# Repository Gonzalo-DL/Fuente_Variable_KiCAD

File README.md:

Fuente de potencia variable con 2x LM317.

Ambos tienen la corriente limitada a aprox 1.5A.

Además uno de los dos lados tiene un limitador de corriente regulable hecho con otro LM317.

Ambos lados tienen las tierras separadas y hay salidas para conectar displays de voltage y corriente, switches y conectores.

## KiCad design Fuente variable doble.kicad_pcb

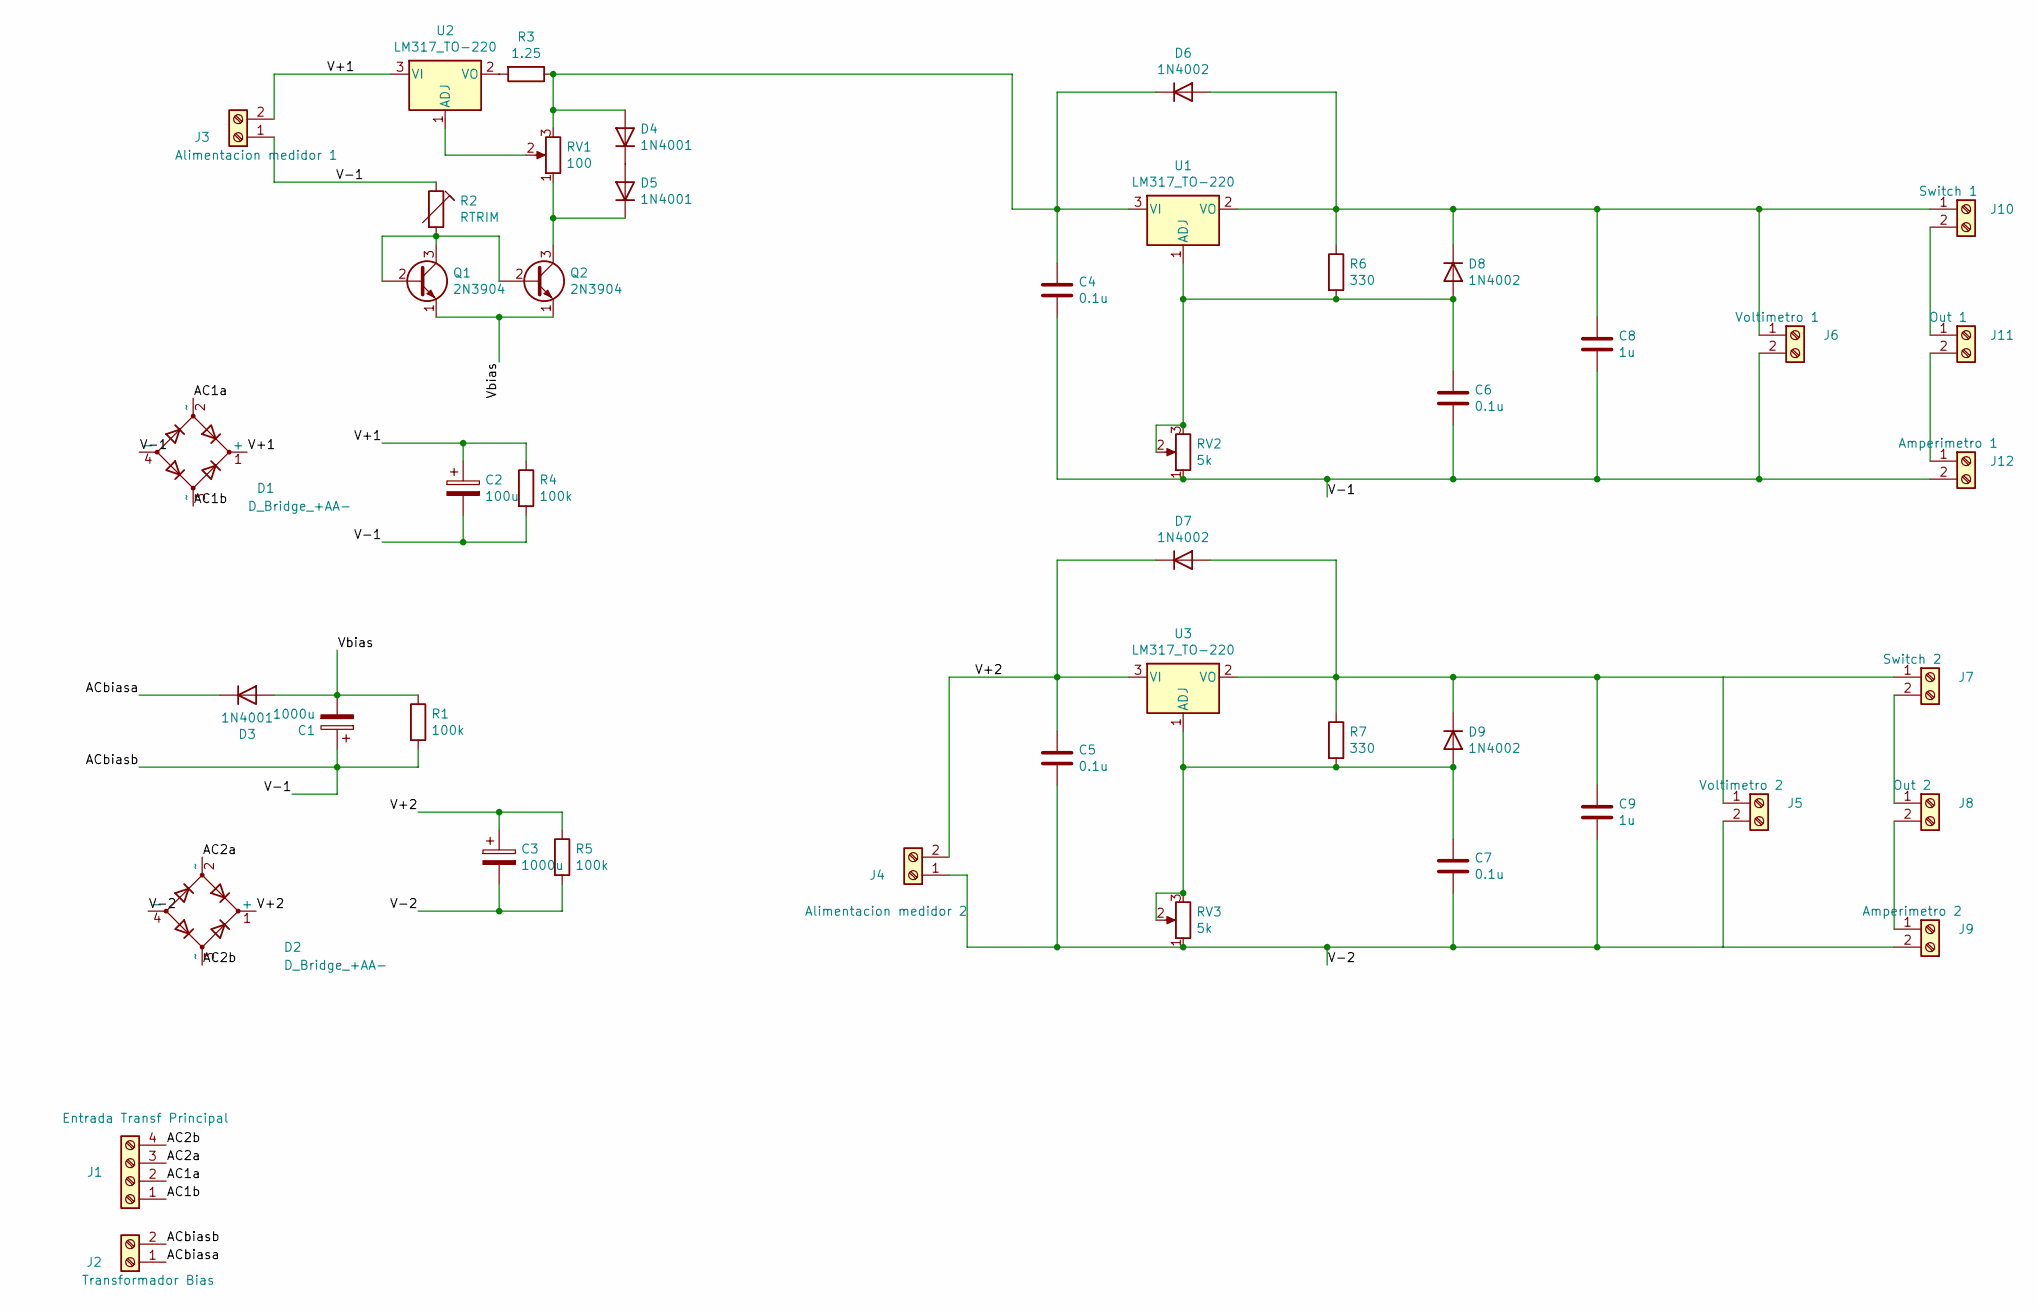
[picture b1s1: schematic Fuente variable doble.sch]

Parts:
C1, C3: 1000u; CP_Radial_D22.0mm_P10.00mm_SnapIn
C2: 100u; CP_Radial_D22.0mm_P10.00mm_SnapIn
C4, C5, C6, C7: 0.1u; C_Disc_D5.1mm_W3.2mm_P5.00mm
C8, C9: 1u; C_Disc_D5.1mm_W3.2mm_P5.00mm
D1, D2: D_Bridge_+AA-; TerminalBlock_MetzConnect_Type086_RT03404HBLC_1x04_P3.81mm_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
D3, D4, D5: 1N4001; D_DO-41_SOD81_P10.16mm_Horizontal
D6, D7, D8, D9: 1N4002; D_DO-41_SOD81_P10.16mm_Horizontal
J1: Entrada Transf Principal; TerminalBlock_bornier-4_P5.08mm
J2: Transformador Bias; TerminalBlock_bornier-2_P5.08mm
J3: Alimentacion medidor 1; TerminalBlock_bornier-2_P5.08mm
J4: Alimentacion medidor 2; TerminalBlock_bornier-2_P5.08mm
J5: Voltimetro 2; TerminalBlock_bornier-2_P5.08mm
J6: Voltimetro 1; TerminalBlock_bornier-2_P5.08mm
J7: Switch 2; TerminalBlock_bornier-2_P5.08mm
J8: Out 2; TerminalBlock_bornier-2_P5.08mm
J9: Amperimetro 2; TerminalBlock_bornier-2_P5.08mm
J10: Switch 1; TerminalBlock_bornier-2_P5.08mm
J11: Out 1; TerminalBlock_bornier-2_P5.08mm
J12: Amperimetro 1; TerminalBlock_bornier-2_P5.08mm
Q1, Q2: 2N3904; TO-92_Inline
R1, R4, R5: 100k; R_Axial_DIN0207_L6.3mm_D2.5mm_P10.16mm_Horizontal
R2: RTRIM; Potentiometer_Runtron_RM-063_Horizontal
R3: 1.25; R_Axial_DIN0207_L6.3mm_D2.5mm_P10.16mm_Horizontal
R6, R7: 330; R_Axial_DIN0207_L6.3mm_D2.5mm_P10.16mm_Horizontal
RV1: 100; Potentiometer_Alps_RK163_Single_Horizontal
RV2, RV3: 5k; Potentiometer_Alps_RK163_Single_Horizontal
U1, U2, U3: LM317_TO-220; TO-220-3_Vertical

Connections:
/AC1a: D1.2 (~~), J1.2
/AC1b: D1.3 (~~), J1.1
/AC2a: D2.2 (~~), J1.3
/AC2b: D2.3 (~~), J1.4
/ACbiasa: D3.1 (K), J2.1
/ACbiasb: C1.1, C2.2, C4.2, C6.2, C8.2, D1.4 (-), J2.2, J3.1, J6.2, J12.2, R1.2, R2.1, R4.2, RV2.1
/V+1: C2.1, D1.1 (+), J3.2, R4.1, U2.3 (VI)
/V+2: C3.1, C5.1, D2.1 (+), D7.1 (K), J4.2, R5.1, U3.3 (VI)
/V-2: C3.2, C5.2, C7.2, C9.2, D2.4 (-), J4.1, J5.2, J9.2, R5.2, RV3.1
/Vbias: C1.2, D3.2 (A), Q1.1 (E), Q2.1 (E), R1.1
unnamed: C4.1, D4.2 (A), D6.1 (K), R3.1, RV1.3, U1.3 (VI)
unnamed: C6.1, D8.2 (A), R6.2, RV2.2, RV2.3, U1.1 (ADJ)
unnamed: C7.1, D9.2 (A), R7.2, RV3.2, RV3.3, U3.1 (ADJ)
unnamed: C8.1, D6.2 (A), D8.1 (K), J6.1, J10.1, R6.1, U1.2 (VO)
unnamed: C9.1, D7.2 (A), D9.1 (K), J5.1, J7.1, R7.1, U3.2 (VO)
unnamed: D4.1 (K), D5.2 (A)
unnamed: D5.1 (K), Q2.3 (C), RV1.1
unnamed: J7.2, J8.1
unnamed: J8.2, J9.1
unnamed: J10.2, J11.1
unnamed: J11.2, J12.1
unnamed: Q1.2 (B), Q1.3 (C), Q2.2 (B), R2.2
unnamed: R3.2, U2.2 (VO)
unnamed: RV1.2, U2.1 (ADJ)

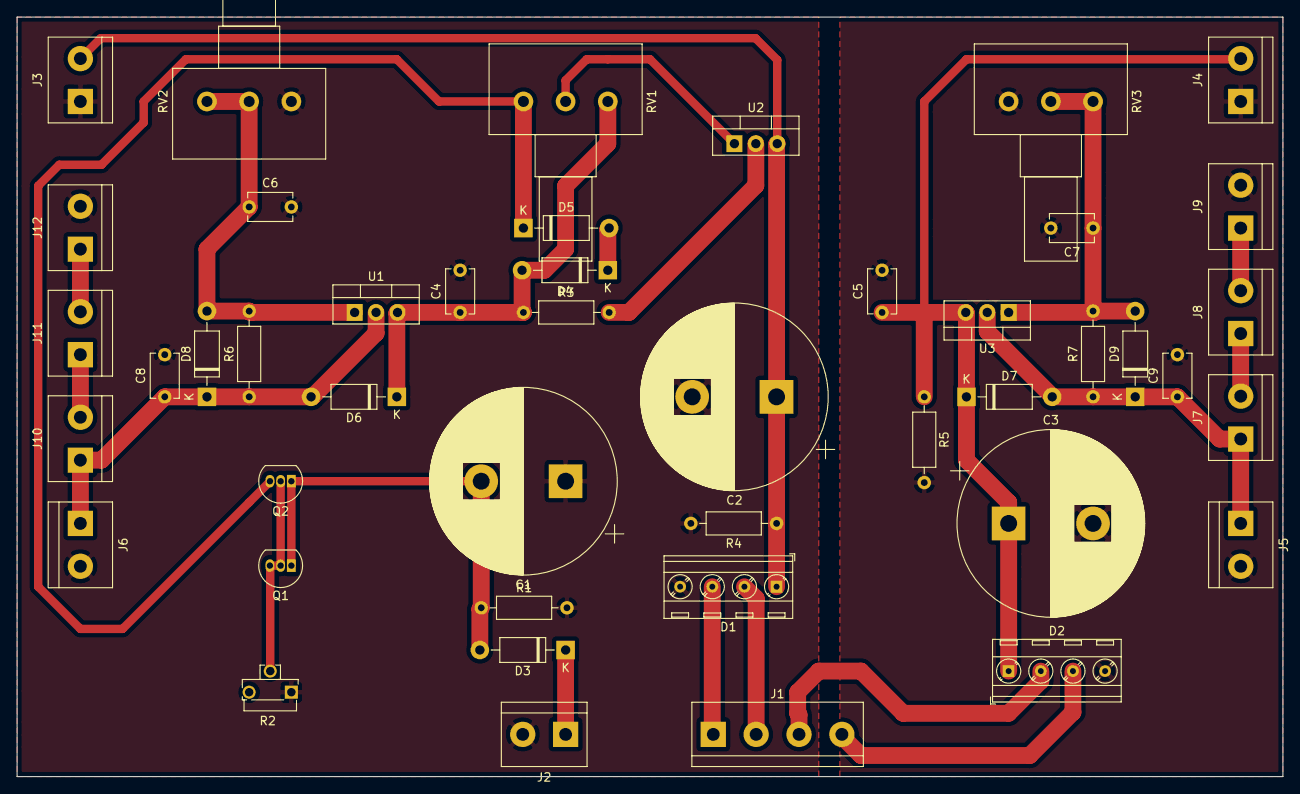
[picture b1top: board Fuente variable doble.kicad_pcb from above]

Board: 2 copper layers, 150.0 x 90.0 mm, 45 parts (0 on the bottom side), 24 nets.

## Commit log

2021-07-28 Upload README.md
